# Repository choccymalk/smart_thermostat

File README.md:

# smart_thermostat
 A smart thermostat

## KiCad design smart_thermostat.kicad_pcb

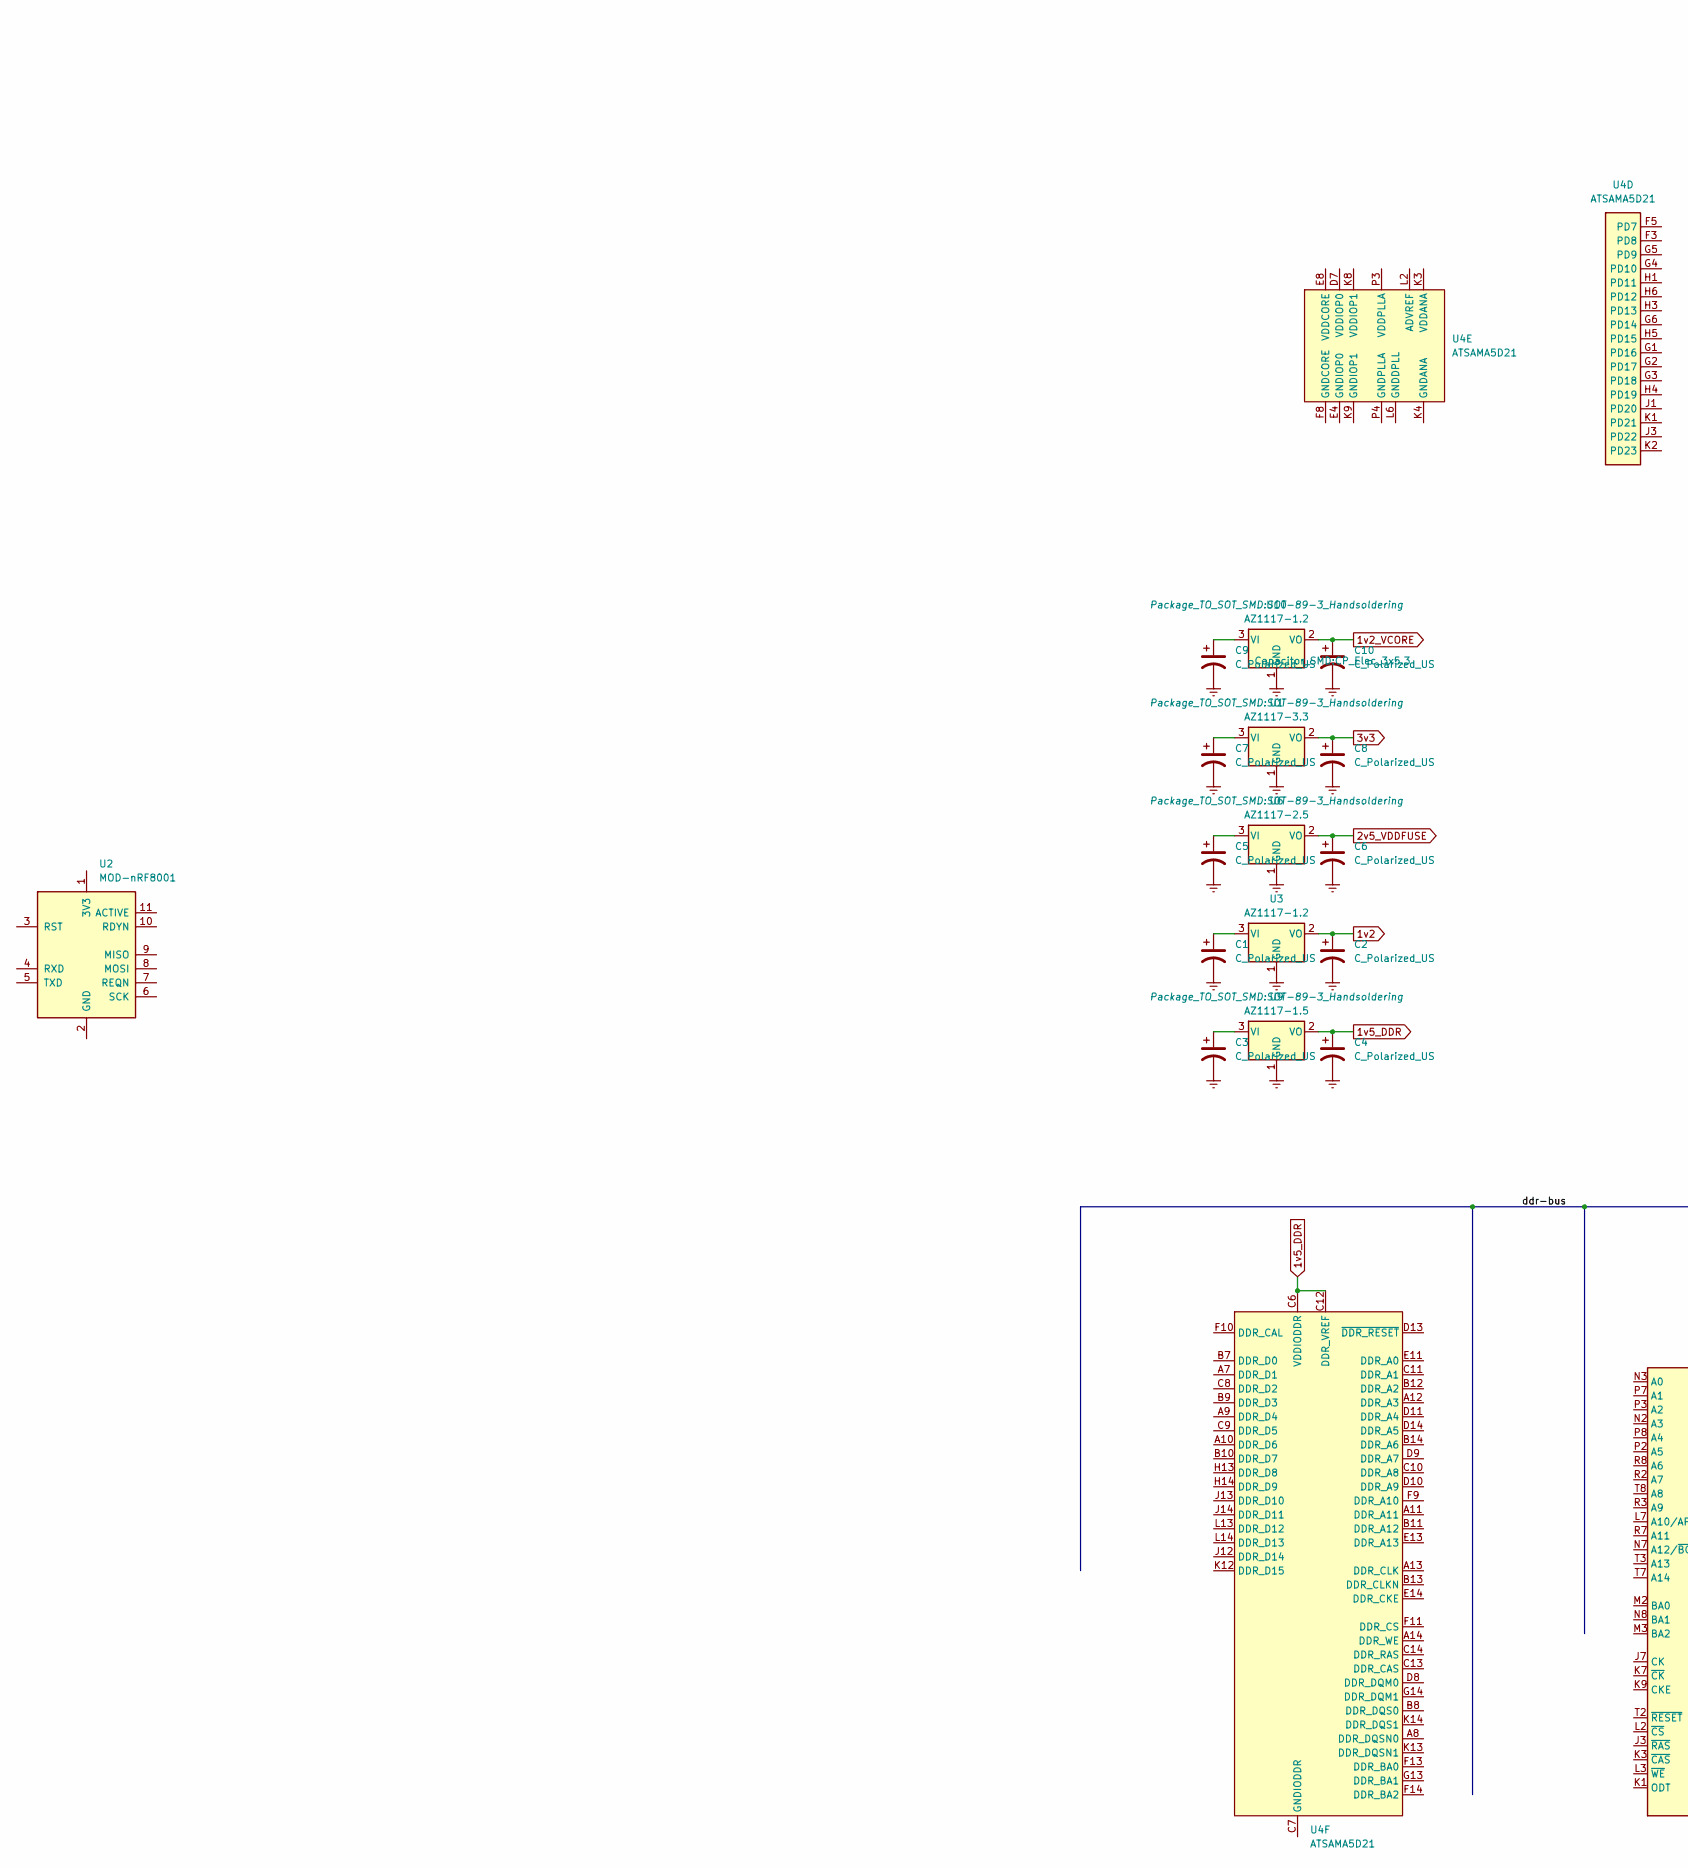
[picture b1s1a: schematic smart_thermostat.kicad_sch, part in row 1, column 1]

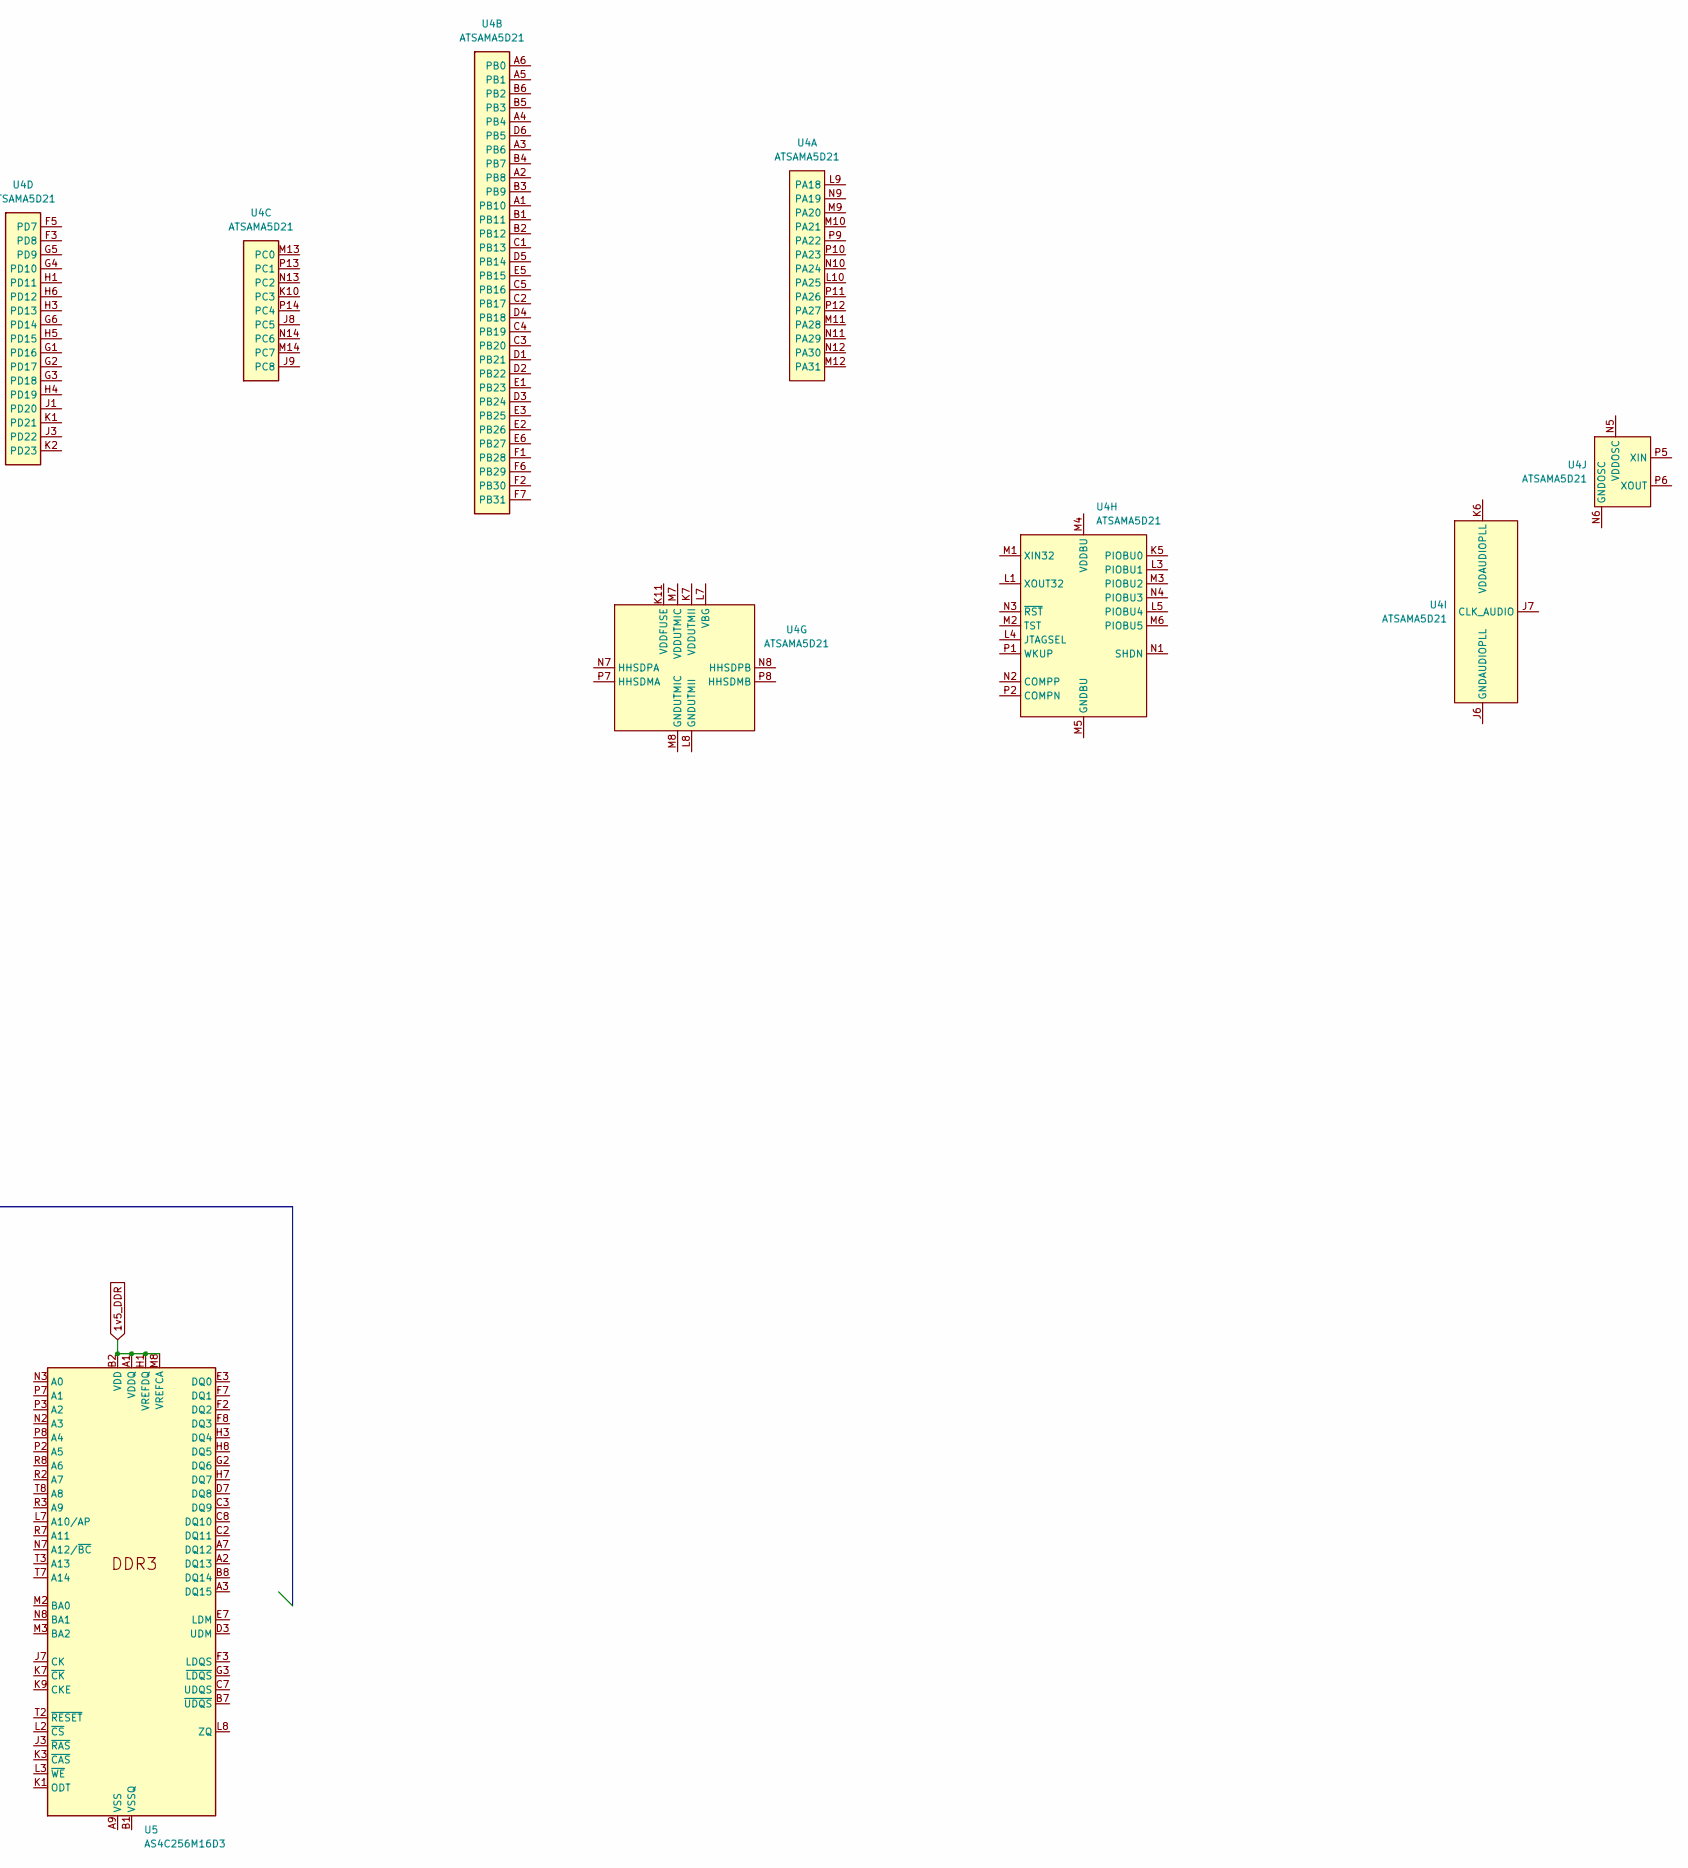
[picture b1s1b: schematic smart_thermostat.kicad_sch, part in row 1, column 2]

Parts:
C1, C2, C3, C4, C5, C6, C7, C8, C9, C10: C_Polarized_US; CP_Elec_3x5.3
U1: AZ1117-3.3; SOT-89-3_Handsoldering
U2: MOD-nRF8001
U3, U10: AZ1117-1.2; SOT-89-3_Handsoldering
U4: ATSAMA5D21; Microchip_TFBGA-196_11x11mm_Layout14x14_P0.75mm_SMD
U5: AS4C256M16D3; BGA-96_9.0x13.0mm_Layout2x3x16_P0.8mm
U6: AZ1117-2.5; SOT-89-3_Handsoldering
U9: AZ1117-1.5; SOT-89-3_Handsoldering

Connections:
1v2: C2.1, U3.2 (VO)
1v2_VCORE: C10.1, U10.2 (VO)
1v5_DDR: C4.1, U4.C6 (VDDIODDR), U4.C12 (DDR_VREF), U4.E10 (VDDIODDR), U4.E12 (VDDIODDR), U4.G10 (VDDIODDR), U4.G12 (VDDIODDR), U4.H11 (VDDIODDR), U4.H12 (DDR_VREF), U4.J10 (VDDIODDR), U5.A1 (VDDQ), U5.A8 (VDDQ), U5.B2 (VDD), U5.C1 (VDDQ), U5.C9 (VDDQ), U5.D2 (VDDQ), U5.D9 (VDD), U5.E9 (VDDQ), U5.F1 (VDDQ), U5.G7 (VDD), U5.H1 (VREFDQ), U5.H2 (VDDQ), U5.H9 (VDDQ), U5.K2 (VDD), U5.K8 (VDD), U5.M8 (VREFCA), U5.N1 (VDD), U5.N9 (VDD), U5.R1 (VDD), U5.R9 (VDD), U9.2 (VO)
2v5_VDDFUSE: C6.1, U6.2 (VO)
3v3: C8.1, U1.2 (VO)
Earth: C1.2, C2.2, C3.2, C4.2, C5.2, C6.2, C7.2, C8.2, C9.2, C10.2, U1.1 (GND), U3.1 (GND), U6.1 (GND), U9.1 (GND), U10.1 (GND)
unnamed: C7.1, U1.3 (VI)
unnamed: C1.1, U3.3 (VI)
unnamed: U4.J2 (GNDANA), U4.K4 (GNDANA)
unnamed: U4.F8 (GNDCORE), U4.G7 (GNDCORE), U4.G9 (GNDCORE), U4.H7 (GNDCORE), U4.J4 (GNDCORE)
unnamed: U4.E4 (GNDIOP0), U4.E7 (GNDIOP0)
unnamed: U4.K9 (GNDIOP1), U4.L12 (GNDIOP1)
unnamed: U4.H2 (VDDANA), U4.K3 (VDDANA)
unnamed: U4.E8 (VDDCORE), U4.G8 (VDDCORE), U4.H8 (VDDCORE), U4.H9 (VDDCORE), U4.J5 (VDDCORE)
unnamed: U4.D7 (VDDIOP0), U4.F4 (VDDIOP0)
unnamed: U4.K8 (VDDIOP1), U4.L11 (VDDIOP1)
unnamed: U4.C7 (GNDIODDR), U4.D12 (GNDIODDR), U4.E9 (GNDIODDR), U4.F12 (GNDIODDR), U4.G11 (GNDIODDR), U4.H10 (GNDIODDR), U4.J11 (GNDIODDR)
unnamed: U5.A9 (VSS), U5.B3 (VSS), U5.E1 (VSS), U5.G8 (VSS), U5.J2 (VSS), U5.J8 (VSS), U5.M1 (VSS), U5.M9 (VSS), U5.P1 (VSS), U5.P9 (VSS), U5.T1 (VSS), U5.T9 (VSS)
unnamed: U5.B1 (VSSQ), U5.B9 (VSSQ), U5.D1 (VSSQ), U5.D8 (VSSQ), U5.E2 (VSSQ), U5.E8 (VSSQ), U5.F9 (VSSQ), U5.G1 (VSSQ), U5.G9 (VSSQ)
unnamed: C5.1, U6.3 (VI)
unnamed: C3.1, U9.3 (VI)
unnamed: C9.1, U10.3 (VI)

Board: 2 copper layers, 18 parts (0 on the bottom side), 22 nets, no tracks yet.

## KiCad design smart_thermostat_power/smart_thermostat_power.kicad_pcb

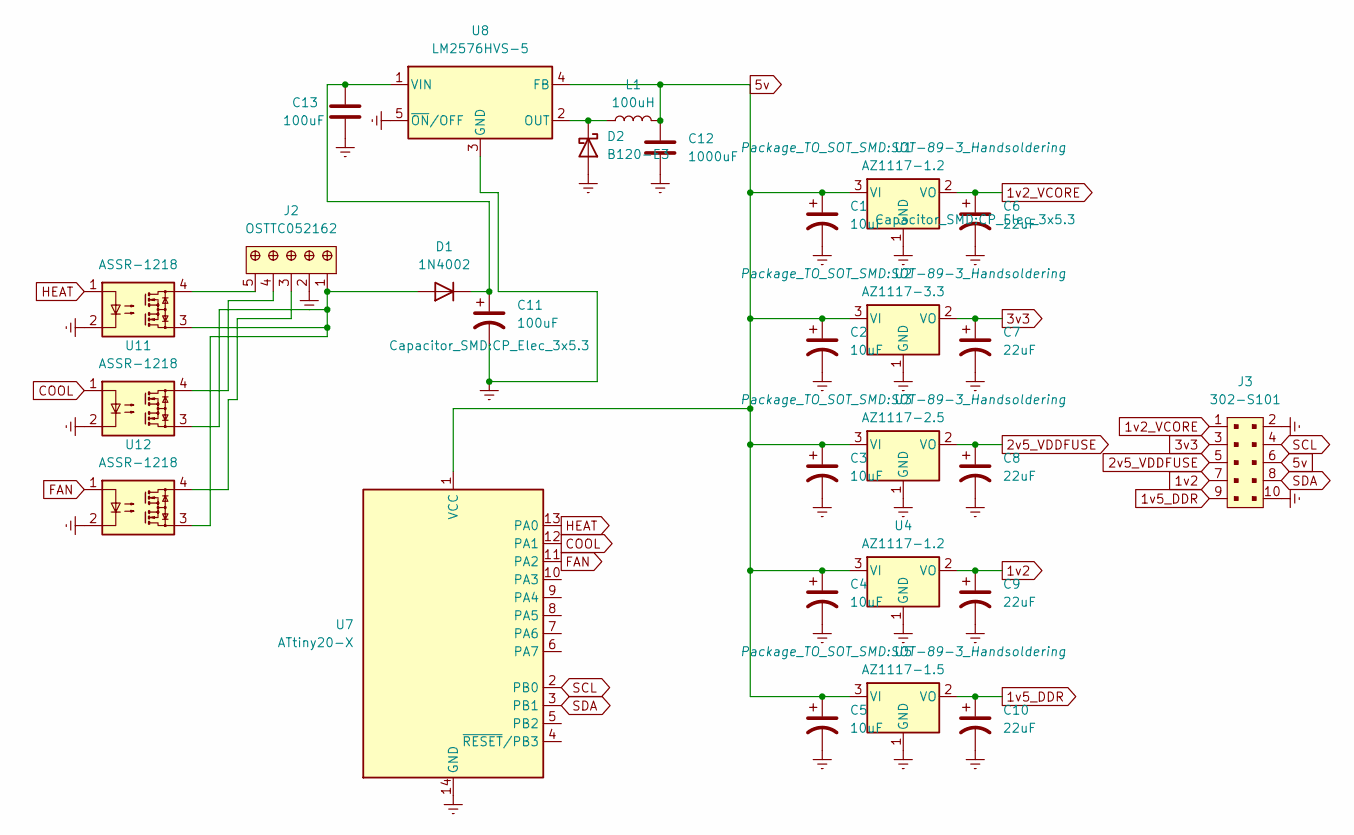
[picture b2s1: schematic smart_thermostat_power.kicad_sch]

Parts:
C1, C2, C3, C4, C5: 10uF; CP_Elec_3x5.3
C6, C7, C8, C9, C10: 22uF; CP_Elec_3x5.3
C11: 100uF; CP_Elec_3x5.3
C12: 1000uF; C_1210_3225Metric_Pad1.33x2.70mm_HandSolder
C13: 100uF; C_1210_3225Metric_Pad1.33x2.70mm_HandSolder
D1: 1N4002; D_DO-41_SOD81_P10.16mm_Horizontal
D2: B120-E3; D_SMA-SMB_Universal_Handsoldering
J2: OSTTC052162; Term_Block_1x5_P5.08mm; MPN OSTTC052162; Digi-Key_PN ED2612-ND
J3: 302-S101; PinHeader_2x5_P2.54mm_Drill1.2mm; MPN 302-S101; Digi-Key_PN ED1543-ND
L1: 100uH; L_6.3x6.3_H3
U1, U4: AZ1117-1.2; SOT-89-3_Handsoldering
U2: AZ1117-3.3; SOT-89-3_Handsoldering
U3: AZ1117-2.5; SOT-89-3_Handsoldering
U5: AZ1117-1.5; SOT-89-3_Handsoldering
U7: ATtiny20-X; TSSOP-14_4.4x5mm_P0.65mm
U8: LM2576HVS-5; TO-263-5_TabPin3
U10, U11, U12: ASSR-1218; SO-4_4.4x4.3mm_P2.54mm

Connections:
1v2: C9.1, J3.7, U4.2 (VO)
1v2_VCORE: C6.1, J3.1, U1.2 (VO)
1v5_DDR: C10.1, J3.9, U5.2 (VO)
2v5_VDDFUSE: C8.1, J3.5, U3.2 (VO)
3v3: C7.1, J3.3, U2.2 (VO)
5v: C1.1, C2.1, C3.1, C4.1, C5.1, C12.1, J3.6, L1.2, U1.3 (VI), U2.3 (VI), U3.3 (VI), U4.3 (VI), U5.3 (VI), U7.1 (VCC), U8.4 (FB)
COOL: U7.12 (PA1), U11.1
Earth: C1.2, C2.2, C3.2, C4.2, C5.2, C6.2, C7.2, C8.2, C9.2, C10.2, C11.2, C12.2, C13.2, D2.2 (A), J2.2, J3.2, J3.10, U1.1 (GND), U2.1 (GND), U3.1 (GND), U4.1 (GND), U5.1 (GND), U7.14 (GND), U8.3 (GND), U8.5 (~ON/OFF), U10.2, U11.2, U12.2
FAN: U7.11 (PA2), U12.1
HEAT: U7.13 (PA0), U10.1
unnamed: D1.2 (A), J2.1, U10.3, U11.3, U12.3
unnamed: C11.1, C13.1, D1.1 (K), U8.1 (VIN)
unnamed: D2.1 (K), L1.1, U8.2 (OUT)
unnamed: J2.3, U12.4
unnamed: J2.4, U11.4
unnamed: J2.5, U10.4
SCL: J3.4, U7.2 (PB0)
SDA: J3.8, U7.3 (PB1)

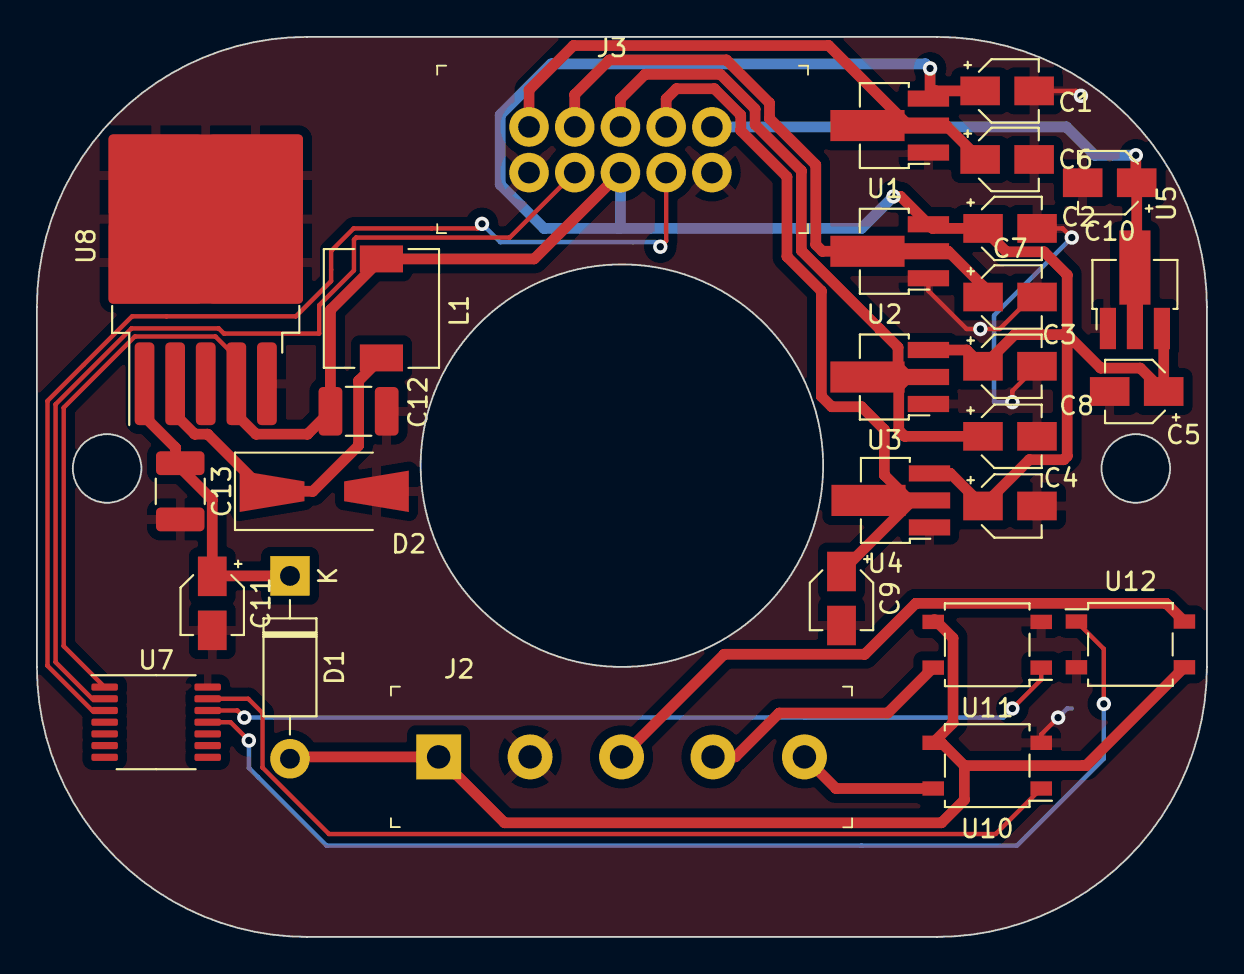
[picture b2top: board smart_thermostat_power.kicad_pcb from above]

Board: 2 copper layers, 65.0 x 50.0 mm, 28 parts (0 on the bottom side), 18 nets.
